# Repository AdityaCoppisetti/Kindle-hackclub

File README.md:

hey im dhruv coppisetti and i built my own kindle from scratch using a e ink display and my own custom pcb i designed!
i absolutely love e ink displays and have been wanting to build my own kindle from a very long time. 
i dont want something thats too fancy or has too much, a simple kindle type design works aswell.

i love reading books and with all the travelling that im doing, i havent been able to carry my books and i know i could 
just download books on my phone and read them that way but i am just a sucker for single purpose technology. 
and its just so amazing building your own devices and with the hackclub's macondo program i thought i should make this and so i did. 
before this i havent really made much without using what was in my arduino kit. so in this project, i learnt along the way whatever it took me to make this 
and you can learn aswell from my journal.md in this project , i go over almost everything

here is how the kindle i designed looks like 

 i need to answer some questions to explain further why i built this 

1) why am i making this?
  this is a device for students and avid readers like me who want a distraction free reading device     with a long battery life and its open sourced.

2) what makes it different from a kindle?
  its fully open sourced hardware and firmware , its extremely repairable , expandable with a microsd card with customizable software and a secondary oled status display for battery , page nuber and reading progress.

 3) display size - 4.2 inch e ink display 
 4) battery life- target of 3 to 6 weeks of normal reading with aggressive deep sleep and infrequent e ink refreshes
 5) linux or bare metal?
    bare metal sice im using an esp32-c3 ( arduino framework with platformIO) this provides much
    lower power consumption and faster startup than linux
6) touchscreen? no physical buttons only for a distraction free reading
experience and improved battery life.

for this project ill be making my own custom esp32 powered pcb 

which looks like this -

it took me multiple versions of the pcb to come to this point you can find all of that in my journal.md 

here is how the pcb looks like in kicad's 3d viewer

and obviously here is a lil 360 

https://github.com/user-attachments/assets/d5890601-8e93-464f-907f-b951f2e43e23

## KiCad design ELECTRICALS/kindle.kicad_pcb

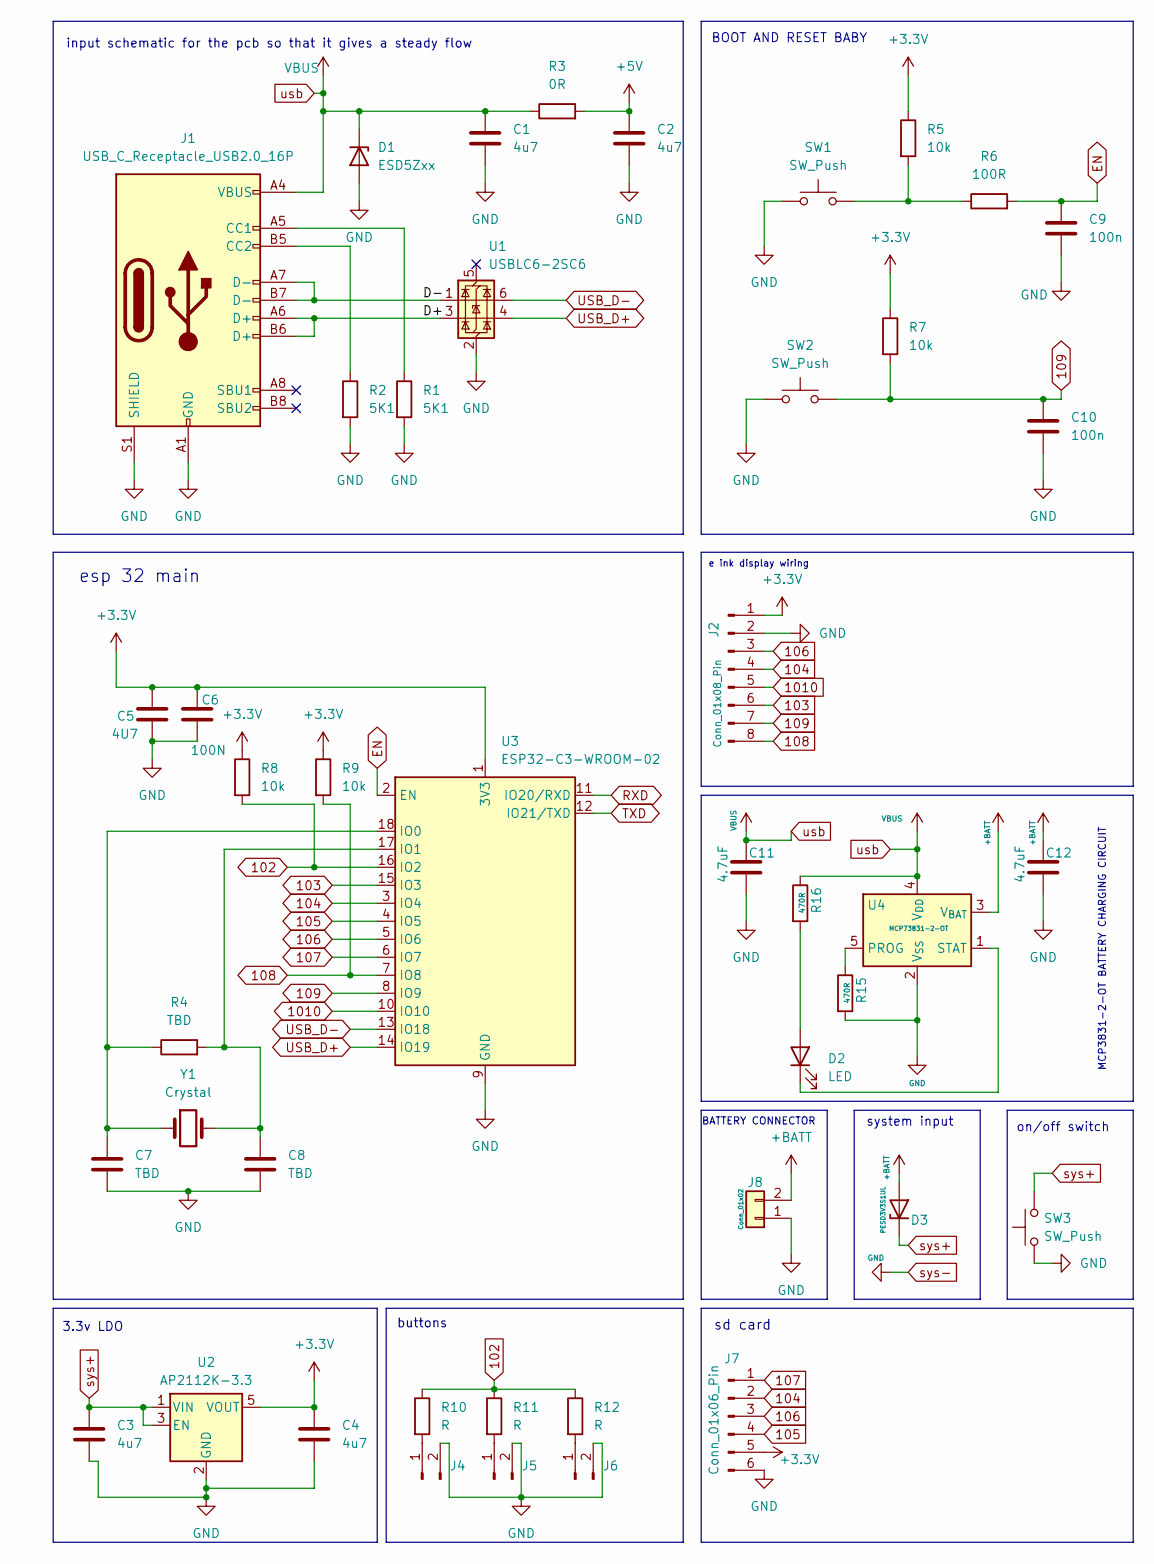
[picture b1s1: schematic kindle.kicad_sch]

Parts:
C1, C2, C3, C4: 4u7; C_0805_2012Metric
C5: 4U7; C_0805_2012Metric
C6: 100N; C_0402_1005Metric
C7, C8: TBD; C_0201_0603Metric
C9, C10: 100n; C_0402_1005Metric
C11, C12: 4.7uF; C_0805_2012Metric
D1: ESD5Zxx; D_SOD-882D
D2: LED; LED_0402_1005Metric
D3: PESD3V3S1UL; D_SOD-882
J1: USB_C_Receptacle_USB2.0_16P; USB_C_Receptacle_G-Switch_GT-USB-7010ASV
J2: Conn_01x08_Pin; PinHeader_1x08_P2.00mm_Vertical
J4, J5, J6: Conn_01x02_Pin; PinHeader_1x02_P2.00mm_Vertical
J7: Conn_01x06_Pin; PinHeader_1x06_P2.00mm_Vertical
J8: Conn_01x02; JST_PH_S2B-PH-K_1x02_P2.00mm_Horizontal
R1, R2: 5K1; R_0402_1005Metric
R3: 0R; R_0805_2012Metric
R4: TBD; R_0201_0603Metric
R5, R7, R8, R9: 10k; R_0402_1005Metric
R6: 100R; R_0402_1005Metric
R10, R11, R12: R; PinHeader_1x02_P2.00mm_Vertical
R15, R16: 470R; R_0805_2012Metric
SW1, SW2: SW_Push; SW_SPST_B3U-1000P
SW3: SW_Push; PinHeader_1x02_P2.00mm_Vertical
U1: USBLC6-2SC6; SOT-23-6
U2: AP2112K-3.3; SOT-23-5
U3: ESP32-C3-WROOM-02
U4: MCP73831-2-OT; SOT-23-5
Y1: Crystal; Crystal_SMD_3215-2Pin_3.2x1.5mm

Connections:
102: R8.2, R10.1, R11.1, R12.1, U3.16 (IO2)
103: J2.6, U3.15 (IO3)
104: J2.4, J7.2, U3.3 (IO4)
105: J7.4, U3.4 (IO5)
106: J2.3, J7.3, U3.5 (IO6)
107: J7.1, U3.6 (IO7)
108: J2.8, R9.2, U3.7 (IO8)
109: C10.1, J2.7, R7.2, SW2.2, U3.8 (IO9)
1010: J2.5, U3.10 (IO10)
+3.3V: C4.1, C5.1, C6.1, J2.1, J7.5, R5.1, R7.1, R8.1, R9.1, U2.5 (VOUT), U3.1 (3V3)
+5V: C2.1, R3.2
+BATT: C12.1, D3.2 (A), J8.2, U4.3 (V_{BAT})
/D+: J1.A6 (D+), J1.B6 (D+), U1.3 (I/O2)
/D-: J1.A7 (D-), J1.B7 (D-), U1.1 (I/O1)
EN: C9.1, R6.2, U3.2 (EN)
unnamed: D2.2 (A), R16.2
unnamed: D2.1 (K), U4.1 (STAT)
unnamed: J1.A5 (CC1), R1.1
unnamed: J1.B5 (CC2), R2.1
unnamed: J4.1, R10.2
unnamed: J5.1, R11.2
unnamed: J6.1, R12.2
unnamed: R5.2, R6.1, SW1.2
unnamed: C7.1, R4.1, U3.18 (IO0), Y1.1
unnamed: C8.1, R4.2, U3.17 (IO1), Y1.2
unnamed: R15.1, U4.5 (PROG)
RXD: U3.11 (IO20/RXD)
TXD: U3.12 (IO21/TXD)
USB_D+: U1.4 (I/O2), U3.14 (IO19)
USB_D-: U1.6 (I/O1), U3.13 (IO18)
sys+: C3.1, D3.1 (K), SW3.2, U2.1 (VIN), U2.3 (EN)
sys-: C1.2, C2.2, C3.2, C4.2, C5.2, C6.2, C7.2, C8.2, C9.2, C10.2, C11.2, C12.2, D1.2 (A), J1.A1 (GND), J1.A12 (GND), J1.B1 (GND), J1.B12 (GND), J1.S1 (SHIELD), J2.2, J4.2, J5.2, J6.2, J7.6, J8.1, R1.2, R2.2, R15.2, SW1.1, SW2.1, SW3.1, U1.2 (GND), U2.2 (GND), U3.9 (GND), U3.19 (GND), U4.2 (V_{SS})
usb: C1.1, C11.1, D1.1 (K), J1.A4 (VBUS), J1.A9 (VBUS), J1.B4 (VBUS), J1.B9 (VBUS), R3.1, R16.1, U4.4 (V_{DD})

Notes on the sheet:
input schematic for the pcb so that it gives a steady flow
BATTERY CONNECTOR
on/off switch
BOOT AND RESET BABY
3.3v LDO
MCP3831-2-OT BATTERY CHARGING CIRCUIT
system input
buttons
sd card
esp 32 main
e ink display wiring

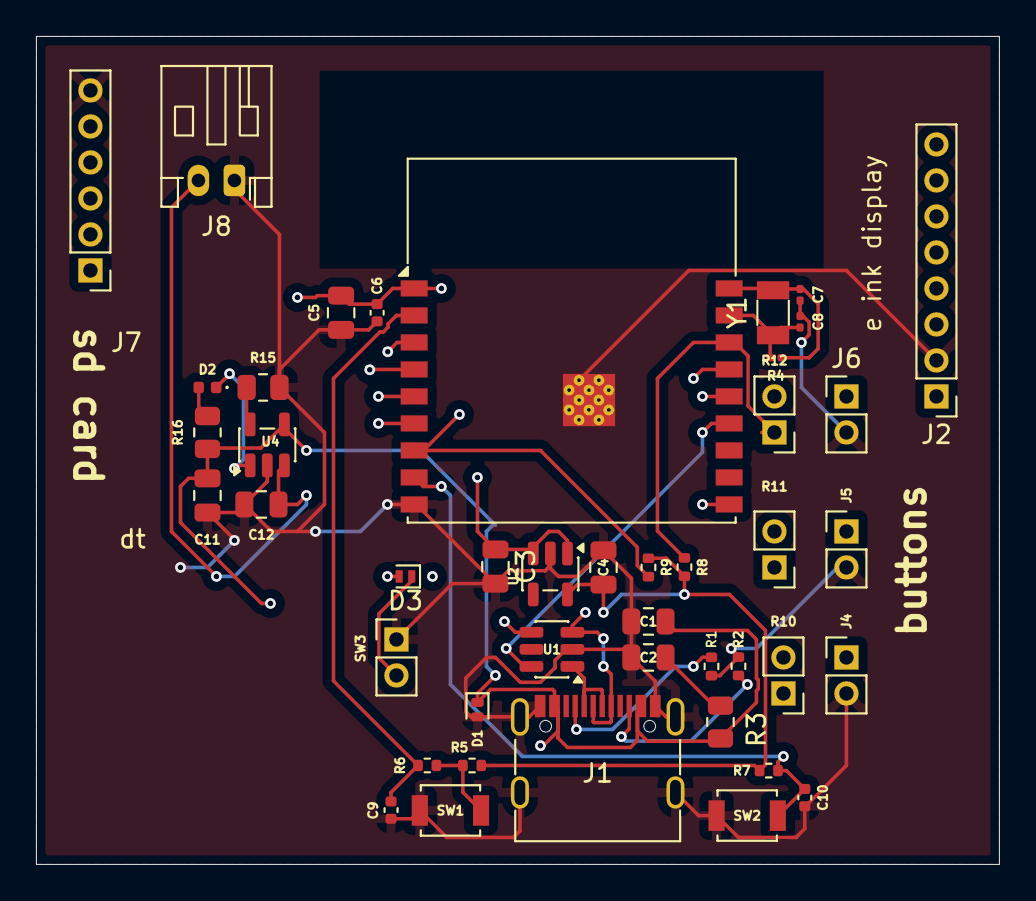
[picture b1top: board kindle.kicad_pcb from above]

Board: 4 copper layers, 53.5 x 46.0 mm, 44 parts (0 on the bottom side), 31 nets.

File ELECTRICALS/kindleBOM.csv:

Reference,KiCad Qty,Value,Footprint,Product,Purchase Qty,Currency,Unit Price,Pack/Line Price,Product Link,in usd
"C1,C2,C3,C4,C5",25,4u7,C_0805_2012Metric,4.7µF 0805 SMD capacitor,10,INR,14,140,https://robu.in/product/mc0805f475z160ct-multicomp-pro-cap-s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,$1.47
C6,1,C,C_0402_1005Metric,4.7µF 0402 SMD capacitor,5,INR,6,30,https://robu.in/product/155r61a475meaad-murata-cap-smd-mlcc-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,$0.31
C9,1,4U7,C_0805_2012Metric,4.7µF 0805 SMD capacitor,10,INR,14,140,https://robu.in/product/mc0805f475z160ct-multicomp-pro-cap-s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,already have
C10,1,100N,C_0402_1005Metric,100nF 0402 SMD capacitor,5,INR,0.55,2.75,https://robu.in/product/0402b104k500nt-fh-50v-100nf-x7r%c2%b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,$0.03
C11,1,4.7u,C_0805_2012Metric,4.7µF 0805 SMD capacitor,10,INR,14,140,https://robu.in/product/mc0805f475z160ct-multicomp-pro-cap-s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,already have
D1,1,D,D_SOD-882D,PMEG3002AELD SOD-882D Schottky diode,5,INR,10,50,https://robu.in/product/pmeg3002aeld315-nexperia-30v-480mv20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,$0.52
D2,1,LED,LED_0402_1005Metric,0402 red SMD LED,5,INR,1.58,7.9,https://robu.in/product/0402-surface-mount-led-red-50pcs/,$0.08
J1,1,USB_C_Receptacle_USB2.0_16P,USB_C_Receptacle_G-Switch_GT-USB-7010ASV,G-Switch GT-USB7010ASV USB-C receptacle,1,USD,0.44,0.44,https://jlcpcb.com/partdetail/GSwitch-GT_USB7010ASV/C2988369,$0.44
J2,1,Conn_01x02,JST_PH_S2B-PH-K_1x02_P2.00mm_Horizontal,JST PH 2-pin 2.00mm horizontal connector,5,USD,0.68,,https://robu.in/product/s2b-ph-klfsn-jst-1x2p-2p-ph-tin-2-25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,$0.68
J3,1,Conn_01x08_Pin,PinHeader_1x08_P2.00mm_Vertical,1x8 2.00mm pitch pin header,10,USD,0.42,4.2,https://robu.in/product/ds1021-09-1x8sf1-a3-0-b6-0-b-connfly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,$0.42
"J4,J5",4,Conn_01x06_Pin,PinHeader_1x06_P2.00mm_Vertical,1x6 2.00mm pitch pin header,10,USD,0.42,,https://robu.in/product/ds1021-09-1x8sf1-a3-0-b6-0-b-connfly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,$0.42
"R1,R2",4,5K1,R_0402_1005Metric,5.1kΩ 0402 SMD resistor,5,USD,0.04,,https://robu.in/product/ac0402fr-075k1l-yageo-res-thick-film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,$0.04
R3,1,0r,R_0402_1005Metric,0Ω 0402 SMD resistor,5,USD,0.013,,https://robu.in/product/erj2ge0r00x-panasonic-100mw-thick-fi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,$0.01
"R4,R6,R8,R9",16,10k,R_0402_1005Metric,10kΩ 0402 SMD resistor,10,USD,0.082,,https://robu.in/product/10k-resistor-smdr-0402-pack-of-50/,$0.08
R5,1,100r,R_0402_1005Metric,100Ω 0402 SMD resistor,2,,,,https://robu.in/product/1-month-warranty-1125/,$0.03
R10,1,470r,R_0402_1005Metric,470Ω 0402 SMD resistor,3,USD,0.0068,,https://robu.in/product/ac0402fr-07470rl-yageo-res-thick-fil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,$0.01
R11,1,470r,R_0805_2012Metric,470Ω 0805 SMD resistor,4,USD,0.042,,https://robu.in/product/rc0805fr-07470rl-yageo-res-thick-fil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,$0.04
"R12,R13,R14",9,R,PinHeader_1x02_P2.00mm_Vertical,1x2 2.00mm pitch pin header,5,USD,0.42,,https://robu.in/product/ds1021-09-1x8sf1-a3-0-b6-0-b-connfly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,$0.42
"SW1,SW2",4,SW_Push,SW_SPST_B3U-1000P,Omron B3U-1000P SMD tactile switch,6,USD,3.99,3.99,https://robu.in/product/b3u-1000p-omron-2-5mm-1-6mm-round-bu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,$3.99
"SW3,SW4,SW5,SW6",16,SW_Push,PinHeader_1x02_P2.00mm_Vertical,1x2 2.00mm connector/header,7,USD,0.23,,https://robu.in/product/aa07a09010000006a-bzcn-3a-125v-3a-25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,$0.23
U1,1,USBLC6-2SC6,SOT-23-6,USBLC6-2SC6,8,USD,0.47,,https://robu.in/product/usblc6-2sc6-ms-msksemi-4-5a-15v-150w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,$0.47
U2,1,AP2112K-3.3,SOT-23-5,AP2112K-3.3,9,USD,0.94,,https://robu.in/product/ap2128k-3-3trg1-diodes-incorporated-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,$0.95
U3,1,ESP32-C3-WROOM-02,ESP32-C3-WROOM-02,ESP32-C3-WROOM-02,10,USD,8.15,,https://robu.in/product/espressif-esp32-c3-wroom-02-n4-module/,$8.15
U4,1,MCP73831-2-OT,SOT-23-5,MCP73831-2-OT,11,USD,5.35,,https://robu.in/product/mcp73831t-2aci-ot-microchip-battery-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,$5.35
BAT1 (external),,Lithium battery,,SP Rechargeable battery (Amazon listing),12,USD,3.13,,https://www.amazon.in/SP-Rechargeable-Connector-Bluetooth-El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,$3.13
pcb from jlcpcb,,pcb,,pcb,1,USD,2,2,,$2.00
shipping for pcb ,,pcb,,pcb,,,30,30,,$28.00
e ink display,1,e ink display,none, e ink display ,1,inr,,6040,https://amzn.in/d/0fYbejic,$63.29
touch buttons,3,TTP223 Touch Key Switch Module,none,TTP223 Touch Key Switch Module,1,inr,,₹228,https://amzn.in/d/00sZICji,$2.39
,,,,,,,,,,total amount is $122.95
